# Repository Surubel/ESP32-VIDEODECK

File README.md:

# ESP32-VIDEODECK
A development board designed around the ESP 32 WROOM module. Theoretically capable of On Screen Display (OSD) comparable with standard FPV racing drone. 
An 4066 analog switch and an LM1881 sync separator handle the composite video part, with the CH340 acting as a USB bridge. 
The project is documented in more detail at: https://hackaday.io/project/166670-esp32-video-deck

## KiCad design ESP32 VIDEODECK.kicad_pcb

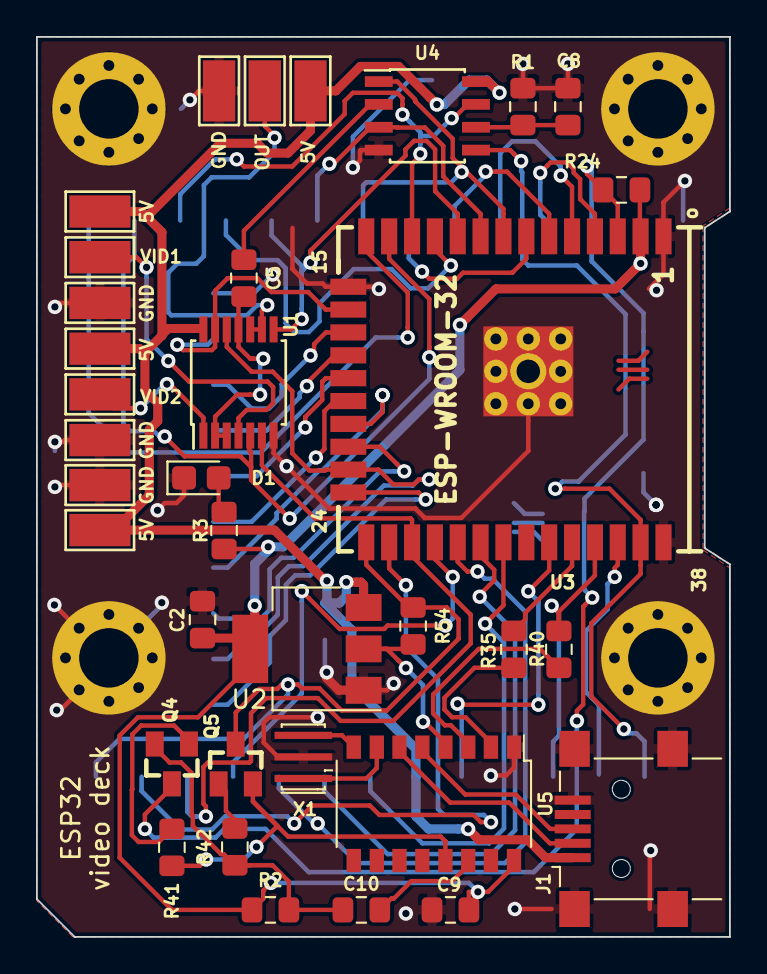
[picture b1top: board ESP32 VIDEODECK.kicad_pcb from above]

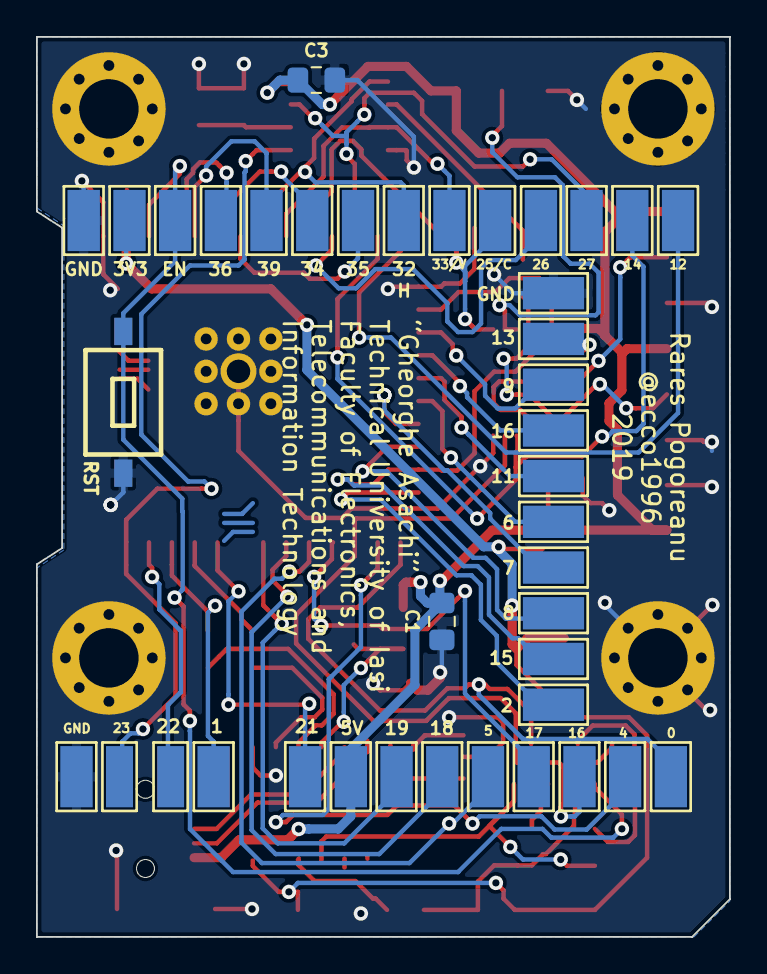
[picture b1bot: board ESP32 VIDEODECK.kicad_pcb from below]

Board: 2 copper layers, 38.5 x 50.0 mm, 79 parts (40 on the bottom side), 54 nets.

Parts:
0, 1, 2, 3V3, 4, 5, 5V, 5V#2, 5V#3, 5V#4, 5V#5, 6, 7, 8, 9, 11, 12, 13, 14, 15, 16, 16#2, 17, 18, 19, 21, 22, 23, 25/C, 26, 27, 32, 33/V, 34, 35, 36, 39: 3V3; TestPoint_Keystone_5015_Micro-Minature
C1, C2, C9, C10: 1n; C_0805_2012Metric_Pad1.15x1.40mm_HandSolder
C3, C5, C8: 100nF; C_0805_2012Metric_Pad1.15x1.40mm_HandSolder
D1: ON; LED_0805_2012Metric_Castellated
EN: 3V3; TestPoint_Keystone_5015_Micro-Minature
GND: 3V3; TestPoint_Keystone_5015_Micro-Minature
GND#2, GND#3, GND#4, GND#5, GND#6, GND#7: 3V3; TestPoint_Keystone_5015_Micro-Minature
J1: USB_OTG; USB_Mini-B_Lumberg_2486_01_Horizontal
MH2, MH3, MH3#2, MH3#3: Mounting_hole_Shield_3.3mm
OUT: 3V3; TestPoint_Keystone_5015_Micro-Minature
Q4, Q5: BC817-40(SOT23); SOT23
R1: 560k; R_0805_2012Metric_Pad1.15x1.40mm_HandSolder
R2: 10K; R_0805_2012Metric_Pad1.15x1.40mm_HandSolder
R3: 65R; R_0805_2012Metric_Pad1.15x1.40mm_HandSolder
R24, R41, R42: 1k/R0603; R_0805_2012Metric_Pad1.15x1.40mm_HandSolder
R35, R40: 220R/R0603; R_0805_2012Metric_Pad1.15x1.40mm_HandSolder
R54: NA/R0603; R_0805_2012Metric_Pad1.15x1.40mm_HandSolder
RST: T1107A(6x3,8x2,5MM)
U1: 4066; TSSOP-14_4.4x5mm_P0.65mm
U2: LM1117-3.3; SOT-223-3_TabPin2
U3: ESP-WROOM-32; ESP-WROOM-32_MODULE
U4: LM1881; SOIC-8_3.9x4.9mm_P1.27mm
U5: CH340G; SOP-16_4.4x10.4mm_P1.27mm
VID1, VID2: 3V3; TestPoint_Keystone_5015_Micro-Minature
X1: CSTNE12M0G550000R0; Resonator_SMD_muRata_CSTxExxV-3Pin_3.0x1.1mm_HandSoldering

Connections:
+3V3: 3V3.1, C2.1, C9.2, R2.1, R3.1, R24.1, R54.2, U2.2, U3.2, U5.4, U5.16
+5V: 5V.1, 5V#2.1, 5V#3.1, 5V#4.1, 5V#5.1, C1.2, C3.1, J1.1, U1.14, U2.3, U4.8
/BURST: 23.1, U3.37, U4.5
/DTR: Q5.2, R41.1, U5.13
/ESP_EN: EN.1, Q4.3, R24.2, RST.1, U3.3
/GPI34: 34.1, U3.6
/GPI35: 35.1, U3.7
/GPI36: 36.1, U3.4
/GPI39: 39.1, U3.5
/GPIO0: 0.1, Q5.3, R54.1, U3.25
/GPIO1: 1.1, R40.2, U3.35
/GPIO2: 2.1, U3.24
/GPIO3: R35.2, U3.34
/GPIO4: 4.1, U3.26
/GPIO5: 5.1, U3.29
/GPIO6: 6.1, U3.20
/GPIO7: 7.1, U3.21
/GPIO8: 8.1, U3.22
/GPIO9: 9.1, U3.17
/GPIO10: 16.1, U3.18
/GPIO11: 11.1, U3.19
/GPIO12: 12.1, U3.14
/GPIO13: 13.1, U1.13, U3.16
/GPIO14: 14.1, U1.5, U3.13
/GPIO15: 15.1, U1.12, U3.23
/GPIO16: 16#2.1, U1.6, U3.27
/GPIO17: 17.1, U3.28
/GPIO18: 18.1, U3.30
/GPIO19: 19.1, U3.31
/GPIO21: 21.1, U3.33
/GPIO22: 22.1, U3.36
/GPIO26: 26.1, U3.11
/HSYNC: 32.1, U3.8, U4.1
/OE: 27.1, U3.12, U4.7
/RTS: C10.2, Q4.2, R2.2, R42.1
/RTS?: C10.1, U5.14
/RX: R35.1, U5.2
/TX: R40.1, U5.3
/VID_ESP: 25/C.1, U1.8, U3.10
/VID_IN: C5.2, U1.2, U1.3, U1.11
/VID_IN1: U1.4, VID1.1
/VID_IN2: U1.1, VID2.1
/VID_IN?: C5.1, U4.2
/VID_OUT: OUT.1, U1.9, U1.10
/VSYNC: 33/V.1, U3.9, U4.3
GND: C1.1, C2.2, C3.2, C8.2, C9.1, D1.1, GND.1, GND#2.1, GND#3.1, GND#4.1, GND#5.1, GND#6.1, GND#7.1, J1.5, J1.6, MH2.GND1, MH3.GND1, MH3#2.GND1, MH3#3.GND1, R1.2, RST.2, U1.7, U2.1, U3.1, U3.15, U3.38, U3.39, U4.4, U5.1, X1.2
unnamed: C8.1, R1.1, U4.6
unnamed: D1.2, R3.2
unnamed: J1.2, U5.6
unnamed: J1.3, U5.5
unnamed: Q4.1, R41.2
unnamed: Q5.1, R42.2
unnamed: U5.7, X1.1
unnamed: U5.8, X1.3
